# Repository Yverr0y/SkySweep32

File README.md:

# SkySweep32

Open-source passive multi-band RF monitor and logger built around ESP32-S3.

**855–925 MHz · 2.4 GHz · 5.8 GHz · BLE/Wi-Fi · GNSS · microSD · Web UI**

[English](#english) | [Русский](#russian)

---

## English

SkySweep32 Rev C combines three passive RF observation paths with local
logging, positioning, a display, battery operation, and networking in one
open-source device.

> **Rev C is the current hardware revision.** It is ready for its first
> physical prototype. No Rev C board has yet been physically bench-tested.

### Start here

- [Build Rev C](BUILD_THIS.md) — one concise route to the current prototype.
- [Hardware](hardware/rev_c/README.md) — schematic, PCB, BOM, enclosure, and
  source-of-truth hierarchy.
- [Firmware](#firmware-compatibility) — build the canonical ESP32-S3 target.
- [Roadmap](hardware/rev_c/ROADMAP.md) — physical evidence before refinement.
- [Validation](hardware/rev_c/validation/verification_summary.json) — current
  reproducible CAD/build evidence and its limits.
- [Website](https://bobberdolle1.github.io/SkySweep32/) — product overview in
  English and Russian.

### What SkySweep32 does

- **855–925 MHz:** E07-900M10S/CC1101 channelized RSSI and activity
  observation. 433 MHz is outside the Rev C contract.
- **2.4 GHz:** E28-2G4M12SX/SX1281 instantaneous-RSSI sweep with a dedicated
  internal U.FL antenna.
- **5.8 GHz:** RX5808-based eight-channel analog RSSI observation from
  5645–5945 MHz. Every procured lot needs the documented incoming check.
- **Local device functions:** GNSS logging, microSD storage, OLED status,
  buttons/buzzer, protected battery operation, native USB, Wi-Fi dashboard,
  BLE receive functions, and ESP-NOW source support.

These are passive energy/RSSI observation paths. They do not identify a
protocol or transmitter, demodulate video, provide RF direction finding, or
perform active RF interference.

### Rev C hardware

- `ESP32-S3-WROOM-1-N16R8` with native USB-C programming.
- Ebyte `E07-900M10S`, Ebyte `E28-2G4M12SX`/SX1281, and a
  procurement-qualified `RX5808-2012-12P` envelope.
- u-blox `SAM-M10Q-00B`, Molex `104031-0811` microSD socket, and Adafruit
  `PID 326` OLED on a keyed harness.
- Protected USB-C/battery power path using BQ24074, TPS61232, MAX17048, and
  AP63203WU-7 with the specified protected Adafruit `PID 328` battery.
- 150 × 95 mm four-layer PCB with a continuous L2 ground reference.
- 165.4 × 117.4 × 33.5 mm printed indoor enclosure generated around the PCBA,
  battery, display, antennas, harnesses, and M3 hardware. It is not sealed or
  IP rated.

See the [Rev C architecture](hardware/rev_c/ARCHITECTURE.md) and
[exact component manifest](hardware/rev_c/hardware_manifest.json) for the
canonical implementation.

### Capabilities and limits

`Implemented in source` is not physical validation.

| Capability | Rev C implementation | Current limit |
|---|---|---|
| 855–925 MHz observation | E07/CC1101 RSSI/activity | RF response unmeasured; no protocol identity |
| 2.4 GHz observation | E28/SX1281 instantaneous RSSI | Coarse energy/activity only; no demodulation |
| 5.8 GHz observation | RX5808 channel selection + analog RSSI | Supplier/pinout and RF response need physical checks |
| Wi-Fi / BLE | ESP32-S3 dashboard and receive functions | No physical Rev C run; Remote ID has no conformance evidence |
| GNSS / storage / display | Exact fitted modules and source support | No live-fix, endurance, or physical UI test |
| ESP-NOW | Source support | No range, coexistence, or multi-node bench test |
| TinyML | Excluded from Rev C | Legacy source has a dummy model; trained inference is not implemented |
| LoRa / Meshtastic | Excluded from Rev C motherboard | A possible future external expansion, not Rev C hardware |

### Build and validation

[BUILD_THIS.md](BUILD_THIS.md) is the builder entrypoint. It links to the
fitted BOM, fabrication package, enclosure, assembly procedure, canonical
firmware, and prototype checklist without mixing revisions.

The detailed [Rev C build guide](hardware/rev_c/BUILD.md) requires the
complete local gate before purchase:

```bash
python hardware/rev_c/verify_schematic_parity.py
python hardware/verify.py
```

The verification record includes ERC/DRC results, precise exclusion audit,
CAD interference checks, fabrication exports, and the firmware build. These
are design/CAD results only; they do not establish RF performance, reliability,
compliance, manufacturing yield, or field operation.

### Firmware compatibility

Build the current hardware from source only:

```bash
pio run -e esp32s3_rev_c_passive
pio run -e esp32s3_rev_c_passive --target upload
```

> **Do not flash `v0.6.1` binaries onto Rev C.** They target legacy ESP32 DevKit
> wiring. `esp32dev_base`, `esp32dev_standard`, `esp32dev_pro`, and
> `esp32s3_rev_b_pro` remain compile-checked only for historical regression;
> their pin maps, BOMs, enclosures, and release binaries are incompatible with
> Rev C.

### Validation and engineering history

[Validation](hardware/rev_c/validation/verification_summary.json) records the
exact tools, source revision, commands, evidence paths, ERC/DRC results, and
narrow documented exclusions. A skipped gate is recorded as skipped, never as
passed.

Rev C is the only current hardware source. [Rev B](hardware/rev_b/) is a failed
and unverified historical baseline; [Rev A](hardware/LEGACY_REV_A_STATUS.md) is
legacy parser-compatibility history. Neither may be ordered or used to build
Rev C. See the [engineering audit](hardware/ENGINEERING_AUDIT_2026-08-11.md)
for the evidence.

### License and lawful use

GNU GPL v3. Passive reception can still be regulated and can expose private or
protected information. Follow local radio, privacy, aviation, and data laws.
The canonical hardware contains no active interference functions.

---

## Русский

SkySweep32 Rev C объединяет три тракта пассивного RF-наблюдения с локальным
журналированием, позиционированием, дисплеем, питанием от аккумулятора и
сетевыми функциями в одном open-source устройстве.

> **Rev C — текущая аппаратная ревизия.** Она готова к первому физическому
> прототипу. Физическая плата Rev C ещё не прошла стендовые испытания.

### Начните отсюда

- [Собрать Rev C](BUILD_THIS.md) — короткий маршрут к текущему прототипу.
- [Аппаратная часть](hardware/rev_c/README.md) — схема, PCB, BOM, корпус и
  иерархия источников истины.
- [Прошивка](#совместимость-прошивки) — сборка канонической цели ESP32-S3.
- [Дорожная карта](hardware/rev_c/ROADMAP.md) — сначала физические измерения,
  затем изменения.
- [Валидация](hardware/rev_c/validation/verification_summary.json) —
  воспроизводимые CAD/build-проверки и их ограничения.
- [Сайт проекта](https://bobberdolle1.github.io/SkySweep32/).

### Что делает SkySweep32

- **855–925 МГц:** E07-900M10S/CC1101, канальное пассивное наблюдение RSSI и
  активности. 433 МГц не входит в контракт Rev C.
- **2.4 ГГц:** E28-2G4M12SX/SX1281, обзор мгновенного RSSI с отдельной
  внутренней антенной U.FL.
- **5.8 ГГц:** RX5808, восемь каналов и аналоговый RSSI в диапазоне
  5645–5945 МГц. Каждая закупленная партия требует входного контроля.
- **Локальные функции:** GNSS-журналирование, microSD, OLED, кнопки/зуммер,
  защищённое аккумуляторное питание, native USB, Wi-Fi dashboard, приёмные
  BLE-функции и исходная поддержка ESP-NOW.

Это пассивное наблюдение энергии/RSSI. Устройство не определяет протокол или
передатчик, не демодулирует видео, не выполняет радиопеленгацию и не создаёт
активные радиопомехи.

### Аппаратная часть Rev C

- `ESP32-S3-WROOM-1-N16R8` с программированием через native USB-C.
- Ebyte `E07-900M10S`, Ebyte `E28-2G4M12SX`/SX1281 и проверяемый при приёмке
  габарит `RX5808-2012-12P`.
- u-blox `SAM-M10Q-00B`, разъём microSD Molex `104031-0811` и OLED Adafruit
  `PID 326` на ключевом шлейфе.
- Защищённый тракт USB-C/аккумулятора: BQ24074, TPS61232, MAX17048,
  AP63203WU-7 и защищённый аккумулятор Adafruit `PID 328`.
- Четырёхслойная PCB 150 × 95 мм с непрерывной землёй L2.
- Печатный корпус для помещения 165.4 × 117.4 × 33.5 мм, спроектированный
  вокруг PCBA, аккумулятора, дисплея, антенн, шлейфов и крепежа M3. Он не
  герметичен и не имеет IP-рейтинга.

Каноническая реализация описана в [архитектуре Rev C](hardware/rev_c/ARCHITECTURE.md)
и [точном манифесте компонентов](hardware/rev_c/hardware_manifest.json).

### Возможности и ограничения

`Реализовано в исходном коде` не означает физическую проверку.

| Возможность | Реализация Rev C | Текущее ограничение |
|---|---|---|
| Наблюдение 855–925 МГц | E07/CC1101, RSSI/активность | RF-отклик не измерен; протокол не определяется |
| Наблюдение 2.4 ГГц | E28/SX1281, мгновенный RSSI | Только энергия/активность; без демодуляции |
| Наблюдение 5.8 ГГц | RX5808, каналы + аналоговый RSSI | Нужны входной контроль и RF-измерения |
| Wi-Fi / BLE | Dashboard и приёмные функции ESP32-S3 | Нет запуска на физической Rev C; Remote ID без доказательств соответствия |
| GNSS / storage / display | Точные установленные модули и исходный код | Нет live-fix, endurance или физического UI-теста |
| ESP-NOW | Поддержка в исходном коде | Нет стендовых дальностных и multi-node тестов |
| TinyML | Исключён из Rev C | В legacy-коде фиктивная модель; обученной модели нет |
| LoRa / Meshtastic | Исключён из материнской платы Rev C | Возможное внешнее расширение в будущем, не аппаратная часть Rev C |

### Сборка и валидация

[BUILD_THIS.md](BUILD_THIS.md) — входная страница для сборщика. Она связывает
точный BOM, fabrication package, корпус, инструкцию сборки, каноническую
прошивку и чек-лист прототипа без смешения ревизий.

Подробное [руководство Rev C](hardware/rev_c/BUILD.md) требует перед заказом
выполнить:

```bash
python hardware/rev_c/verify_schematic_parity.py
python hardware/verify.py
```

Запись валидации содержит ERC/DRC, точный аудит исключений, CAD-проверки
коллизий, производственные файлы и сборку прошивки. Это результаты CAD/build,
а не доказательство RF-характеристик, надёжности, соответствия нормам,
производственного выхода или полевой работы.

### Совместимость прошивки

Для текущего устройства собирайте прошивку только из исходного кода:

```bash
pio run -e esp32s3_rev_c_passive
pio run -e esp32s3_rev_c_passive --target upload
```

> **Не прошивайте Rev C бинарными файлами `v0.6.1`.** Они относятся к старой
> разводке ESP32 DevKit. `esp32dev_base`, `esp32dev_standard`, `esp32dev_pro` и
> `esp32s3_rev_b_pro` остались только для compile-check исторических регрессий;
> их pin map, BOM, корпуса и release binaries несовместимы с Rev C.

### Валидация и инженерная история

[Валидация](hardware/rev_c/validation/verification_summary.json) фиксирует
точные инструменты, исходную ревизию, команды, пути к evidence, результаты
ERC/DRC и узкие документированные исключения. Пропущенная проверка всегда
записывается как skipped, а не passed.

Rev C — единственный текущий источник аппаратной части. [Rev B](hardware/rev_b/)
— неудачная и непроверенная историческая база, а
[Rev A](hardware/LEGACY_REV_A_STATUS.md) — legacy-история parser compatibility.
Их нельзя заказывать или использовать для сборки Rev C. Доказательства собраны
в [инженерном аудите](hardware/ENGINEERING_AUDIT_2026-08-11.md).

### Лицензия и законное использование

GNU GPL v3. Пассивный приём может регулироваться законом и может раскрывать
частные или защищённые данные. Соблюдайте местные нормы радио-, privacy-,
aviation- и data-law. Каноническая аппаратная часть не содержит активных помех.

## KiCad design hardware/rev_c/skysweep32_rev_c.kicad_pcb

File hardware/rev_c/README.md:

# SkySweep32 Rev C Passive Monitor

## Maturity

**READY FOR FIRST PHYSICAL PROTOTYPE — NOT PRODUCTION VALIDATED**

Rev C is the only canonical current hardware revision. KiCad 10 ERC/DRC,
firmware compilation, fabrication export, full-PCBA STEP generation, and
FreeCAD interference/service-envelope checks are reproducible from this
directory. No Rev C board has been assembled or powered. The package supports
one engineering prototype spin whose bring-up may require changes; it is not a
mass-production release.

Rev A and Rev B are historical, incompatible, and non-orderable. The revision
decision is in [`ADR_001_NEW_REVISION.md`](ADR_001_NEW_REVISION.md).

## Product boundary

Rev C is a passive receive/energy-observation instrument. It has no RF jamming,
protocol-injection, GPS-denial, LoRa, trained TinyML inference, or RF
direction-finding hardware.

| Function | Rev C implementation | Evidence boundary |
|---|---|---|
| 855–925 MHz | Ebyte `E07-900M10S` / CC1101 RSSI and activity | Schematic/layout checked; RF response unmeasured; no 433 MHz operation |
| 2.4 GHz | Ebyte `E28-2G4M12SX` / SX1281 RSSI sweep | Firmware contract and CAD checked; no RF calibration or protocol identity |
| 5.8 GHz | Qualified-envelope `RX5808-2012-12P`, eight selected channels and analog RSSI | Source/pinout/calibration must pass incoming inspection and bench test |
| Wi-Fi/BLE | ESP32-S3 receive functions, web UI, ESP-NOW, experimental Remote ID | Firmware compiles; no physical or standards-conformance test |
| Position/time | u-blox `SAM-M10Q-00B` | UART/TIMEPULSE contract checked; no live-fix test |
| Storage | Molex `104031-0811` microSD | SPI/card-detect contract checked; no card test |
| Display/controls | Adafruit PID 326 OLED on PID 4210 keyed cable, LED, buzzer, three buttons | CAD fit/actuation checked; no physical operation test |
| Portable power | Adafruit PID 328 protected 1S LiPo through BQ24074 power path | Electrical/CAD design checked; charge, runtime, thermal, and safety behavior unmeasured |

The exact parts, GPIO allocation, exclusions, power contract, assembly items,
and mechanical datums are in
[`hardware_manifest.json`](hardware_manifest.json). Manufacturer documentation
defines physical reality; the KiCad schematic and PCB define the manufactured
circuit and geometry.

## Electrical design

- MCU: Espressif `ESP32-S3-WROOM-1-N16R8`, 16 MB flash and 8 MB octal PSRAM.
- USB: GCT `USB4105-GF-A`; 5 V source rated at least 2 A; 5.1 kΩ CC pull-downs;
  no USB-PD voltage negotiation.
- Protection: Bourns `MF-MSMF200-2`, Littelfuse `SMAJ5.0A`, and ST
  `USBLC6-2SC6`.
- Battery/power path: Adafruit `PID 328 / LP785060` protected 1S pack,
  `BQ24074RGTR` at 800 mA charge and 1.3 A input limit.
- Rails: `TPS61232DRCR` fixed 5 V boost with `SRN6028C-1R0Y`, then
  `AP63203WU-7` 3.3 V / 2 A buck with `SRN6028-3R9M`.
- Encoded peak estimate: 1.35 A. This is a design input, not a measured current
  or thermal result.
- Programming: native ESP32-S3 USB, manual BOOT/RESET, and labelled UART0 and
  power test pads.
- Optional vibration output parts are DNP and excluded from fitted BOM and
  placement exports.

## Build this revision

Use [BUILD.md](BUILD.md) as the single first-prototype procurement, assembly,
and source-build path. It links the exact fabrication package, fitted BOM,
non-PCB accessories, first-power limits, and canonical PlatformIO environment.
Do not use any Rev A/Rev B document or `v0.6.1` binary for Rev C.

The hierarchy starts at
[`skysweep32_rev_c.kicad_sch`](skysweep32_rev_c.kicad_sch): overview plus five
functional sheets for power, control/alerts, 2.4 GHz/sub-GHz, 5.8 GHz, and
GNSS/storage/display. `verify_schematic_parity.py` proves its named
reference/pin/net contract against the pre-hierarchy review baseline.

The native KiCad schematic is
[`skysweep32_rev_c.kicad_sch`](skysweep32_rev_c.kicad_sch). Fresh unexcluded
ERC evidence is [`validation/erc.rpt`](validation/erc.rpt); the eight narrowly
documented stock-symbol footprint-filter exceptions are machine-audited in
[`validation/erc_exclusions.json`](validation/erc_exclusions.json).

## PCB construction and routing

Board: 150.0 × 95.0 mm, 1.6 mm nominal, four layers, 3.0 mm corner radius, and
four Ø3.2 mm mounting holes on a 140 × 85 mm pattern.

| Layer | Function | Nominal construction |
|---|---|---|
| L1 / F.Cu | components, USB/RF/power signals, local ground pour | 35 µm copper |
| L2 / GND_PLANE | continuous signal reference plane | 0.18 mm L1–L2 dielectric, 35 µm copper |
| L3 / POWER_PLANE | 3V3 distribution and secondary routing | 1.10 mm core, 35 µm copper |
| L4 / B.Cu | secondary signals and ground pour | 0.18 mm L3–L4 dielectric, 35 µm copper |

Fabricator requirements: FR-4, ENIG, minimum 0.20 mm copper spacing, minimum
0.20 mm finished drill, 0.25 mm default signals, 0.8 mm nominal power traces,
and 0.6/0.3 mm nominal via diameter/drill. USB D+/D− use a 0.25/0.25 mm nominal
geometry and must be field-solver adjusted for 90 Ω differential using the
fabricator's actual stackup. J5 and J7 use short 0.30 mm nominal RF launches and
likewise require 50 Ω confirmation.

L2 remains continuous under signal routes. Antenna keepouts for the
ESP32-S3, GNSS, E28, and E07 paths are free of unrelated copper and parts. The
layout's DRC result proves only the encoded KiCad rules; RF response, USB signal
integrity, power integrity, and manufacturing yield remain unmeasured.

Fresh unexcluded DRC evidence is [`validation/drc.rpt`](validation/drc.rpt).
[`validation/drc_exclusions.json`](validation/drc_exclusions.json) records the
single audited `TPS61232` mixed SMD/thermal-via footprint-type exception.
TP1–TP5 expose protected VBUS, 3V3, GND, UART0 TX, and UART0 RX with the lid
removed.

## Mechanical system

The enclosure generator consumes the complete KiCad PCBA STEP. It includes:

- a protected PID 328 battery bay below the PCBA;
- four DIN 912 M3 × 30 screws, DIN 934 M3 nut traps, PCB supports, and lid
  compression posts at the actual mounting holes;
- USB-C insertion, microSD removal, J5/J7 SMA plug, and external antenna service
  envelopes;
- Adafruit PID 2308 internal 2.4 GHz antenna and its 100 mm U.FL cable envelope;
- lid-mounted Adafruit PID 326 OLED and PID 4210 100 mm cable envelope;
- checked closed and 30 mm-open cable routes;
- independent RESET, BOOT, and USER plungers plus status-LED aperture;
- base, lid, button, service-envelope, open/closed/exploded/cutaway STEP files
  and printable STL parts.

The checked closed outer envelope is 165.4 × 117.4 × 33.5 mm. The case is an
indoor printed enclosure, not sealed and not IP rated. Start the first-fit PETG
print at 0.20 mm layers, four perimeters, and 30% infill. Measure one complete
print and the first PCBA before any batch.

- Generator: [`generate_enclosure.py`](generate_enclosure.py)
- Interface drawing:
  [`enclosure/rev_c_mechanical_drawing.svg`](enclosure/rev_c_mechanical_drawing.svg)
- Machine report:
  [`enclosure/mechanical_validation.json`](enclosure/mechanical_validation.json)
- Assembly/bring-up: [`ASSEMBLY_AND_BRINGUP.md`](ASSEMBLY_AND_BRINGUP.md)
- Physical checks:
  [`PROTOTYPE_VALIDATION_CHECKLIST.md`](PROTOTYPE_VALIDATION_CHECKLIST.md)

Custom RF/GNSS/OLED/battery STEP bodies are explicitly conservative mechanical
envelopes built from referenced drawings. They are not manufacturer precision
CAD. Standard KiCad models are used only where package geometry was checked.
CAD collision checks do not replace sample measurement.

## Evidence roadmap

[ROADMAP.md](ROADMAP.md) defines the mandatory first-board measurements and
the evidence that could justify a later revision. It is deliberately separate
from the current fabrication package: no future feature is part of Rev C until
the required evidence exists.

## Reproducible verification

Requirements are pinned in [`../toolchain.json`](../toolchain.json). From the
repository root:

```bash
python hardware/verify.py
```

The command checks the generated firmware contract, runs ERC/DRC, rebuilds
mechanical envelopes and the PCBA STEP, regenerates case/assembly/drawing files,
runs collision, cable-length, and service-volume checks, regenerates fabrication
files, builds `esp32s3_rev_c_passive`, and refreshes renders. A deliberately
skipped gate is recorded as `SKIPPED`, never `PASS`.

Primary outputs:

- [`validation/verification_summary.json`](validation/verification_summary.json)
- [`manufacturing/fabrication_manifest.json`](manufacturing/fabrication_manifest.json)
- [`manufacturing/bom_fitted.csv`](manufacturing/bom_fitted.csv)
- [`manufacturing/assembly_items.csv`](manufacturing/assembly_items.csv)
- [`manufacturing/positions.csv`](manufacturing/positions.csv)
- [`manufacturing/assembly_top.svg`](manufacturing/assembly_top.svg) and
  [`manufacturing/assembly_bottom.svg`](manufacturing/assembly_bottom.svg):
  primary zoomable fitted-placement/orientation drawings; use
  `positions.csv` for machine assembly and
  [`ASSEMBLY_AND_BRINGUP.md`](ASSEMBLY_AND_BRINGUP.md) for the sequence.
- [`manufacturing/skysweep32_rev_c_gerbers.zip`](manufacturing/skysweep32_rev_c_gerbers.zip)

Do not infer `PROTOTYPE_ASSEMBLED`, `BENCH_TESTED`, `FIELD_TESTED`, or
`PRODUCTION_VALIDATED` from any generated file.

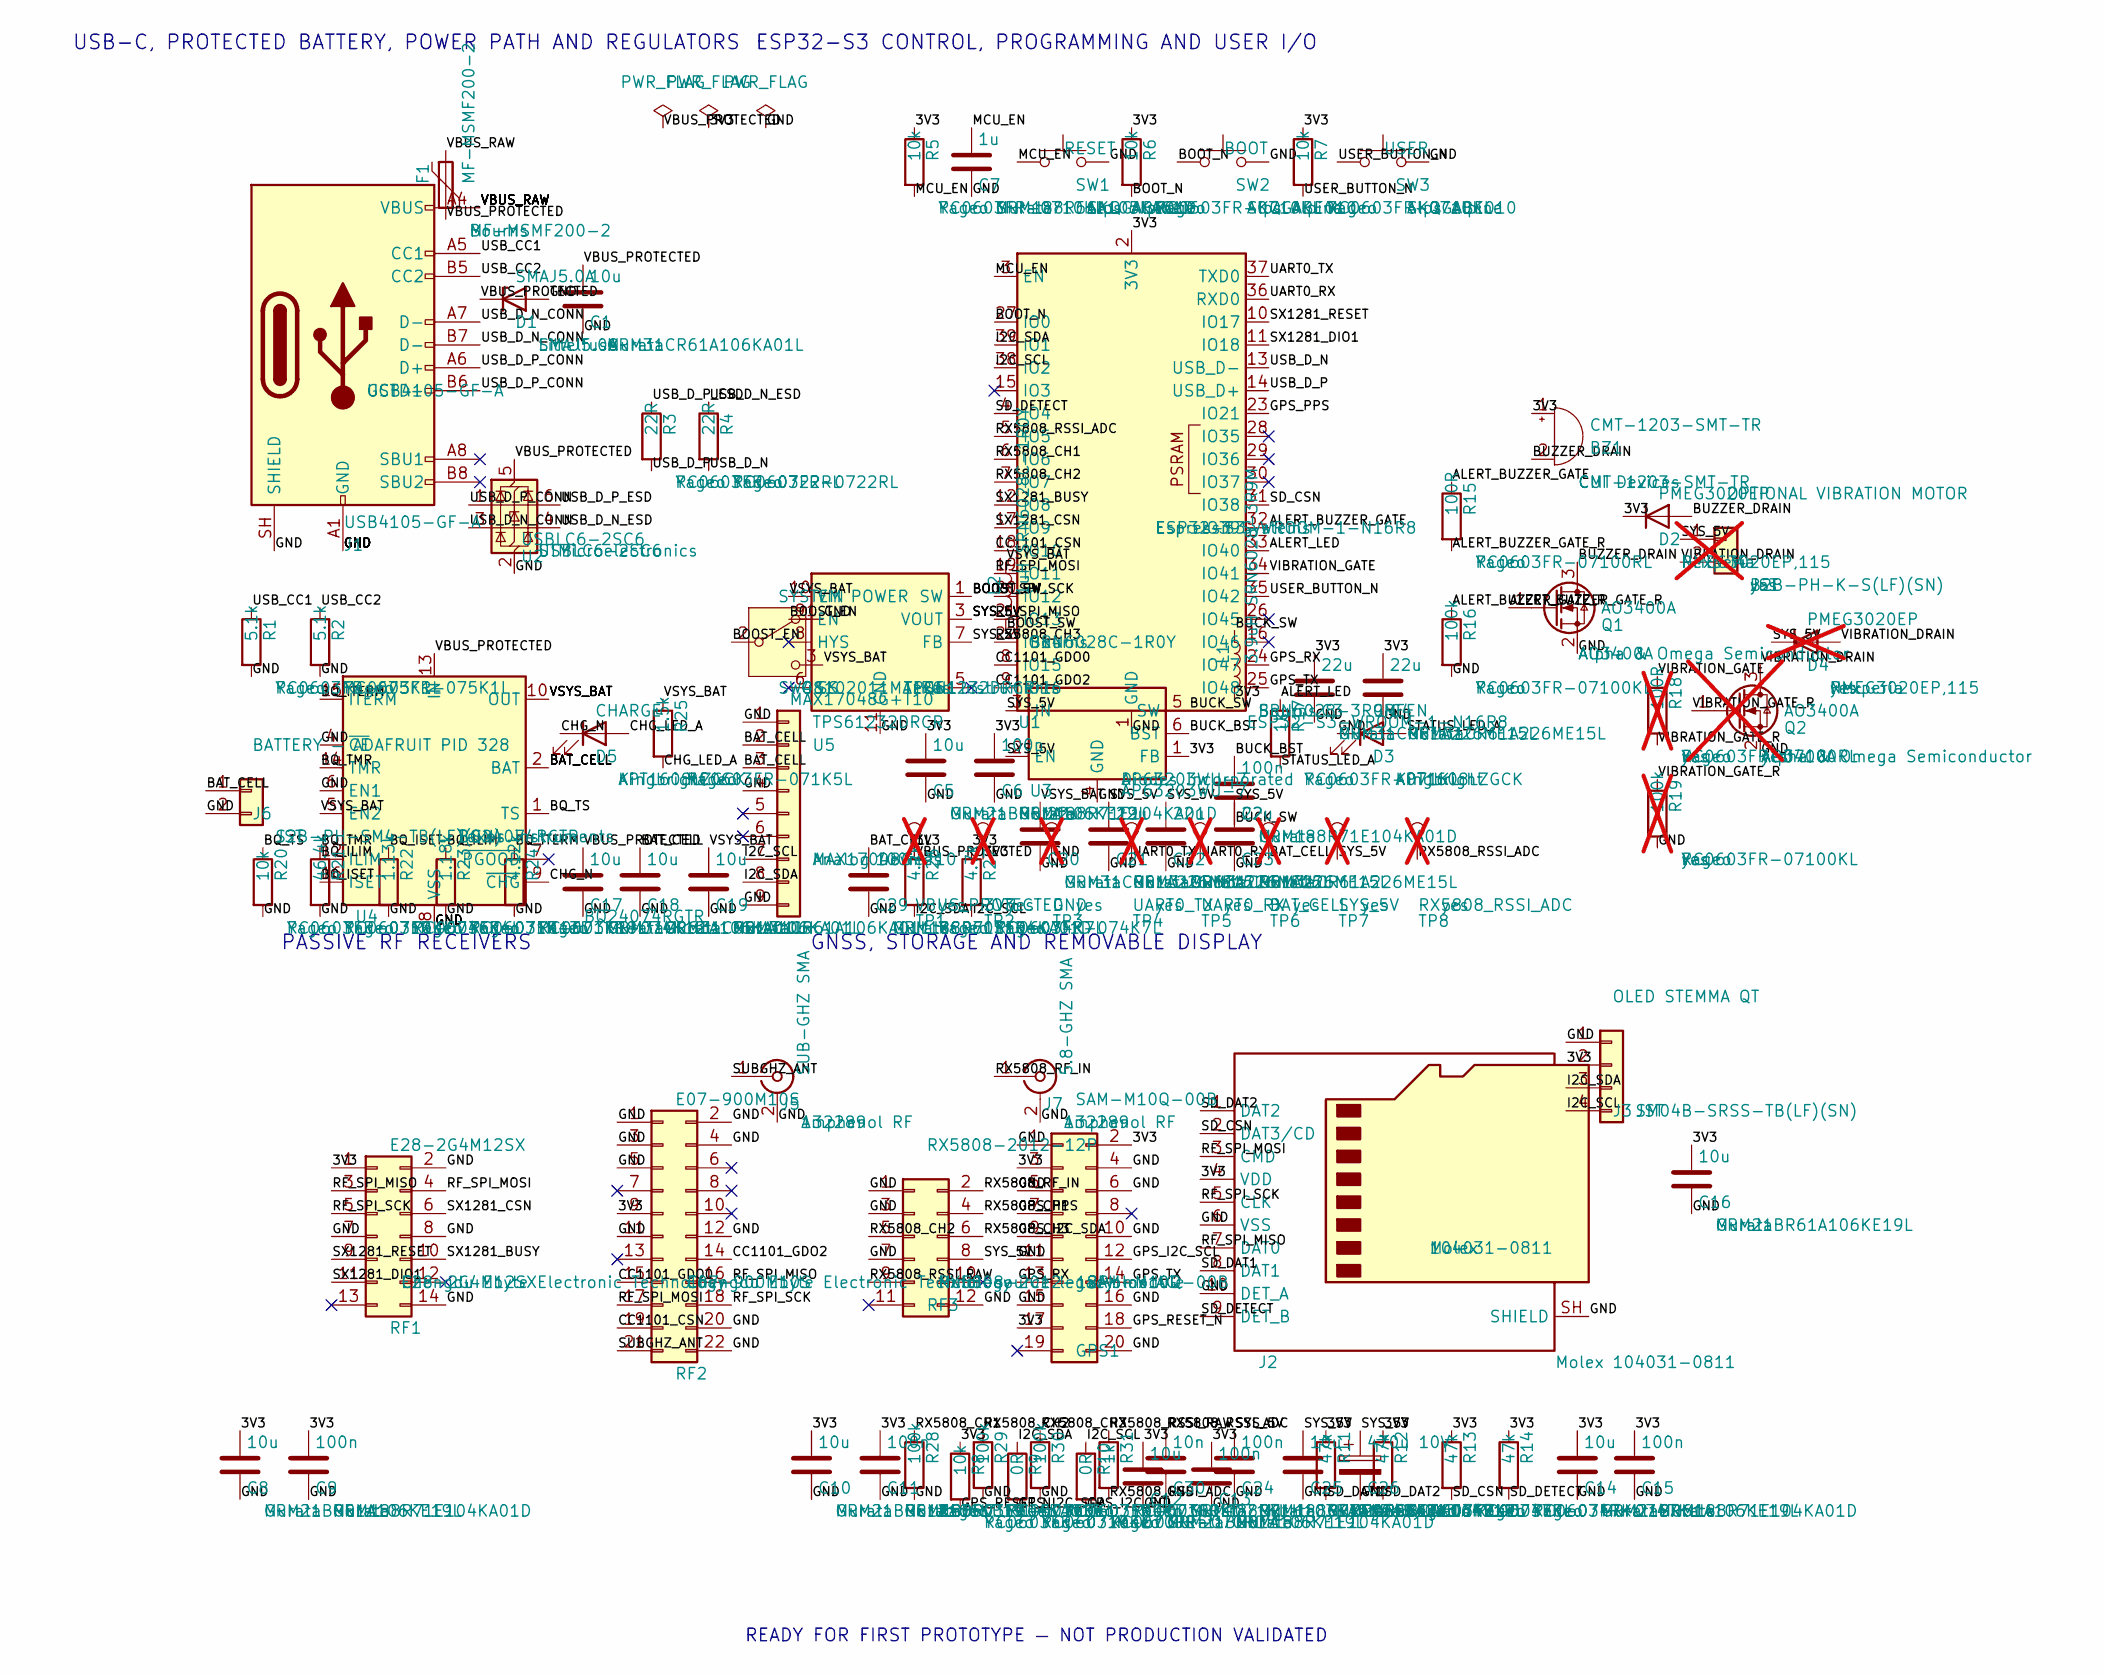
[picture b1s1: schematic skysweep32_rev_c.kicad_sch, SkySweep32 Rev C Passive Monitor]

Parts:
BZ1: CMT-1203-SMT-TR; Buzzer_CUI_CMT_1203_SMT_TR; MPN CMT-1203-SMT-TR
C1, C17, C18, C19: 10u; C_1206_3216Metric; MPN GRM31CR61A106KA01L
C2, C6, C9, C11, C13, C15, C24, C29: 100n; C_0603_1608Metric; MPN GRM188R71E104KA01D
C3, C4, C20, C21, C22, C23: 22u; C_1206_3216Metric; MPN GRM31CR61A226ME15L
C5, C8, C10, C12, C14, C16, C25: 10u; C_0805_2012Metric; MPN GRM21BR61A106KE19L
C7: 1u; C_0603_1608Metric; MPN GRM188R61A105KA61D
C26: 470u 10V; CP_Elec_10x10; MPN EEE-FK1A471P
C30: 10n; C_0603_1608Metric; MPN GRM188R71H103KA01D
D1: SMAJ5.0A; D_SMA; MPN SMAJ5.0A
D2: PMEG3020EP; D_SOD-128; MPN PMEG3020EP,115
D3: GREEN; LED_0603_1608Metric; MPN APT1608LZGCK
D4: PMEG3020EP; D_SOD-128; MPN PMEG3020EP,115; not fitted
D5: CHARGE; LED_0603_1608Metric; MPN APT1608LZGCK
F1: MF-MSMF200-2; Fuse_1812_4532Metric; MPN MF-MSMF200-2
GPS1: SAM-M10Q-00B; Module_UBlox_SAM_M10Q; MPN SAM-M10Q-00B
J1: USB4105-GF-A; USB_C_Receptacle_GCT_USB4105-xx-A_16P_TopMnt_Horizontal; MPN USB4105-GF-A
J2: Molex 104031-0811; microSD_HC_Molex_104031-0811; MPN 104031-0811
J3: OLED STEMMA QT; JST_SH_SM04B-SRSS-TB_1x04-1MP_P1.00mm_Horizontal; MPN SM04B-SRSS-TB(LF)(SN)
J4: OPTIONAL VIBRATION MOTOR; JST_PH_B2B-PH-K_1x02_P2.00mm_Vertical; MPN B2B-PH-K-S(LF)(SN); not fitted
J5: SUB-GHZ SMA; SMA_Amphenol_132289_EdgeMount; MPN 132289
J6: BATTERY — ADAFRUIT PID 328; JST_PH_S2B-PH-SM4-TB_1x02-1MP_P2.00mm_Horizontal; MPN S2B-PH-SM4-TB(LF)(SN)
J7: 5.8-GHZ SMA; SMA_Amphenol_132289_EdgeMount; MPN 132289
L1: 3.9uH SRN6028-3R9M; L_Bourns-SRN6028; MPN SRN6028-3R9M
L2: 1uH SRN6028C-1R0Y; L_Bourns-SRN6028; MPN SRN6028C-1R0Y
Q1: AO3400A; SOT-23; MPN AO3400A
Q2: AO3400A; SOT-23; MPN AO3400A; not fitted
R1, R2: 5.1k; R_0603_1608Metric; MPN RC0603FR-075K1L
R3, R4: 22R; R_0603_1608Metric; MPN RC0603FR-0722RL
R5, R6, R7, R8, R20: 10k; R_0603_1608Metric; MPN RC0603FR-0710KL
R9, R10: 0R; R_0603_1608Metric; MPN RC0603JR-070RL
R11, R12, R13, R14: 47k; R_0603_1608Metric; MPN RC0603FR-0747KL
R15: 100R; R_0603_1608Metric; MPN RC0603FR-07100RL
R16, R28, R29, R30: 100k; R_0603_1608Metric; MPN RC0603FR-07100KL
R17, R31: 1k; R_0603_1608Metric; MPN RC0603FR-071KL
R18: 100R; R_0603_1608Metric; MPN RC0603FR-07100RL; not fitted
R19: 100k; R_0603_1608Metric; MPN RC0603FR-07100KL; not fitted
R21: 46.4k; R_0603_1608Metric; MPN RC0603FR-0746K4L
R22: 1.13k; R_0603_1608Metric; MPN RC0603FR-071K13L
R23: 1.18k; R_0603_1608Metric; MPN RC0603FR-071K18L
R24: 4.12k; R_0603_1608Metric; MPN RC0603FR-074K12L
R25: 1.5k; R_0603_1608Metric; MPN RC0603FR-071K5L
R26, R27: 4.7k; R_0603_1608Metric; MPN RC0603FR-074K7L
RF1: E28-2G4M12SX; Module_Ebyte_E28_2G4M12SX; MPN E28-2G4M12SX
RF2: E07-900M10S; Module_Ebyte_E07_900M10S; MPN E07-900M10S
RF3: RX5808-2012-12P; Module_RX5808_2012_12P; MPN RX5808-2012-12P
SW1: RESET; SW_SPST_SKQG_WithoutStem; MPN SKQGABE010
SW2: BOOT; SW_SPST_SKQG_WithoutStem; MPN SKQGABE010
SW3: USER; SW_SPST_SKQG_WithoutStem; MPN SKQGABE010
SW4: SYSTEM POWER; SW_Slide_SPDT_Angled_CK_OS102011MA1Q; MPN OS102011MA1QN1
TP1: VBUS_PROTECTED; TestPoint_Pad_D1.0mm; not fitted
TP2: 3V3; TestPoint_Pad_D1.0mm; not fitted
TP3: GND; TestPoint_Pad_D1.0mm; not fitted
TP4: UART0_TX; TestPoint_Pad_D1.0mm; not fitted
TP5: UART0_RX; TestPoint_Pad_D1.0mm; not fitted
TP6: BAT_CELL; TestPoint_Pad_D1.0mm; not fitted
TP7: SYS_5V; TestPoint_Pad_D1.0mm; not fitted
TP8: RX5808_RSSI_ADC; TestPoint_Pad_D1.0mm; not fitted
U1: ESP32-S3-WROOM-1-N16R8; ESP32-S3-WROOM-1; MPN ESP32-S3-WROOM-1-N16R8
U2: USBLC6-2SC6; SOT-23-6; MPN USBLC6-2SC6
U3: AP63203WU-7; TSOT-23-6; MPN AP63203WU-7
U4: BQ24074RGTR; VQFN-16-1EP_3x3mm_P0.5mm_EP1.6x1.6mm; MPN BQ24074RGTR
U5: TPS61232DRCR; Texas_S-PVSON-N10_ThermalVias; MPN TPS61232DRCR
U6: MAX17048G+T10; DFN-8-1EP_2x2mm_P0.5mm_EP0.9x1.3mm; MPN MAX17048G+T10

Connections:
3V3: BZ1.1 (+), C3.1, C4.1, C5.1, C6.1, C8.1, C9.1, C10.1, C11.1, C12.1, C13.1, C14.1, C15.1, C16.1, D2.1 (K), GPS1.2, GPS1.3, GPS1.17, J2.4 (VDD), J3.2, L1.2, R5.1, R6.1, R7.1, R8.1, R11.1, R12.1, R13.1, R14.1, R26.1, R27.1, RF1.1, RF2.9, TP2.1, U1.2 (3V3), U3.1 (FB)
ALERT_BUZZER_GATE: R15.1, U1.32 (IO39)
ALERT_BUZZER_GATE_R: Q1.1 (G), R15.2, R16.1
ALERT_LED: R17.1, U1.33 (IO40)
BAT_CELL: C18.1, C29.1, J6.1, TP6.1, U4.2 (BAT), U4.3 (BAT), U6.2, U6.3
BOOST_EN: SW4.2 (B), U5.9 (EN)
BOOST_SW: L2.2, U5.1 (SW), U5.2 (SW)
BOOT_N: R6.2, SW2.1, U1.27 (IO0)
BQ_ILIM: R23.1, U4.12 (ILIM)
BQ_ISET: R22.1, U4.16 (ISET)
BQ_ITERM: R24.1, U4.15 (ITERM)
BQ_TMR: R21.1, U4.14 (TMR)
BQ_TS: R20.1, U4.1 (TS)
BUCK_BST: C2.1, U3.6 (BST)
BUCK_SW: C2.2, L1.1, U3.5 (SW)
BUZZER_DRAIN: BZ1.2 (-), D2.2 (A), Q1.3 (D)
CC1101_CSN: RF2.19, U1.18 (IO10)
CC1101_GDO0: RF2.15, U1.8 (IO15)
CC1101_GDO2: RF2.14, U1.9 (IO16)
CHG_LED_A: D5.2 (A), R25.2
CHG_N: D5.1 (K), U4.9 (~CHG)
GND: C1.2, C3.2, C4.2, C5.2, C6.2, C7.2, C8.2, C9.2, C10.2, C11.2, C12.2, C13.2, C14.2, C15.2, C16.2, C17.2, C18.2, C19.2, C20.2, C21.2, C22.2, C23.2, C24.2, C25.2, C26.2, C29.2, C30.2, D1.2 (A), D3.1 (K), GPS1.1, GPS1.4, GPS1.5, GPS1.6, GPS1.10, GPS1.11, GPS1.15, GPS1.16, GPS1.20, J1.A1 (GND), J1.A12 (GND), J1.B1 (GND), J1.B12 (GND), J1.SH (SHIELD), J2.6 (VSS), J2.10 (DET_A), J2.SH (SHIELD), J3.1, J5.2 (Ext), J6.2, J7.2 (Ext), Q1.2 (S), Q2.2 (S), R1.2, R2.2, R16.2, R19.2, R20.2, R21.2, R22.2, R23.2, R24.2, R28.2, R29.2, R30.2, RF1.2, RF1.7, RF1.8, RF1.14, RF2.1, RF2.2, RF2.3, RF2.4, RF2.5, RF2.11, RF2.12, RF2.20, RF2.22, RF3.1, RF3.3, RF3.7, RF3.12, SW1.2, SW2.2, SW3.2, SW4.1 (A), TP3.1, U1.1 (GND), U1.40 (GND), U1.41 (GND), U2.2 (GND), U3.4 (GND), U4.4 (~CE), U4.6 (EN1), U4.8 (VSS), U4.17 (VSS), U5.11 (GND), U6.1, U6.4, U6.9
GPS_I2C_SCL: GPS1.12, R10.2
GPS_I2C_SDA: GPS1.9, R9.2
GPS_PPS: GPS1.7, U1.23 (IO21)
GPS_RESET_N: GPS1.18, R8.2
GPS_RX: GPS1.13, U1.24 (IO47)
GPS_TX: GPS1.14, U1.25 (IO48)
I2C_SCL: J3.4, R10.1, R27.2, U1.38 (IO2), U6.7
I2C_SDA: J3.3, R9.1, R26.2, U1.39 (IO1), U6.8
MCU_EN: C7.1, R5.2, SW1.1, U1.3 (EN)
RF_SPI_MISO: J2.7 (DAT0), RF1.3, RF2.16, U1.21 (IO13)
RF_SPI_MOSI: J2.3 (CMD), RF1.4, RF2.17, U1.19 (IO11)
RF_SPI_SCK: J2.5 (CLK), RF1.5, RF2.18, U1.20 (IO12)
RX5808_CH1: R28.1, RF3.4, U1.6 (IO6)
RX5808_CH2: R29.1, RF3.5, U1.7 (IO7)
RX5808_CH3: R30.1, RF3.6, U1.22 (IO14)
RX5808_RF_IN: J7.1 (In), RF3.2
RX5808_RSSI_ADC: C30.1, R31.2, TP8.1, U1.5 (IO5)
RX5808_RSSI_RAW: R31.1, RF3.9
SD_CSN: J2.2 (DAT3/CD), R13.2, U1.31 (IO38)
SD_DAT1: J2.8 (DAT1), R11.2
SD_DAT2: J2.1 (DAT2), R12.2
SD_DETECT: J2.9 (DET_B), R14.2, U1.4 (IO4)
STATUS_LED_A: D3.2 (A), R17.2
SUBGHZ_ANT: J5.1 (In), RF2.21
SX1281_BUSY: RF1.10, U1.12 (IO8)
SX1281_CSN: RF1.6, U1.17 (IO9)
SX1281_DIO1: RF1.11, U1.11 (IO18)
SX1281_RESET: RF1.9, U1.10 (IO17)
SYS_5V: C21.1, C22.1, C23.1, C24.1, C25.1, C26.1, D4.1 (K), J4.1, RF3.8, TP7.1, U3.2 (EN), U3.3 (IN), U5.3 (VOUT), U5.4 (VOUT), U5.7 (FB)
UART0_RX: TP5.1, U1.36 (RXD0)
UART0_TX: TP4.1, U1.37 (TXD0)
USB_CC1: J1.A5 (CC1), R1.1
USB_CC2: J1.B5 (CC2), R2.1
USB_D_N: R4.2, U1.13 (USB_D-)
USB_D_N_CONN: J1.A7 (D-), J1.B7 (D-), U2.3 (I/O2)
USB_D_N_ESD: R4.1, U2.4 (I/O2)
USB_D_P: R3.2, U1.14 (USB_D+)
USB_D_P_CONN: J1.A6 (D+), J1.B6 (D+), U2.1 (I/O1)
USB_D_P_ESD: R3.1, U2.6 (I/O1)
USER_BUTTON_N: R7.2, SW3.1, U1.35 (IO42)
VBUS_PROTECTED: C1.1, C17.1, D1.1 (K), F1.2, TP1.1, U2.5 (VBUS), U4.13 (IN)
VBUS_RAW: F1.1, J1.A4 (VBUS), J1.A9 (VBUS), J1.B4 (VBUS), J1.B9 (VBUS)
VIBRATION_DRAIN: D4.2 (A), J4.2, Q2.3 (D)
VIBRATION_GATE: R18.1, U1.34 (IO41)
VIBRATION_GATE_R: Q2.1 (G), R18.2, R19.1
VSYS_BAT: C19.1, C20.1, L2.1, R25.1, SW4.3 (C), U4.5 (EN2), U4.10 (OUT), U4.11 (OUT), U5.10 (VIN)

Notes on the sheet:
USB-C, PROTECTED BATTERY, POWER PATH AND REGULATORS
ESP32-S3 CONTROL, PROGRAMMING AND USER I/O
PASSIVE RF RECEIVERS
GNSS, STORAGE AND REMOVABLE DISPLAY
READY FOR FIRST PROTOTYPE — NOT PRODUCTION VALIDATED

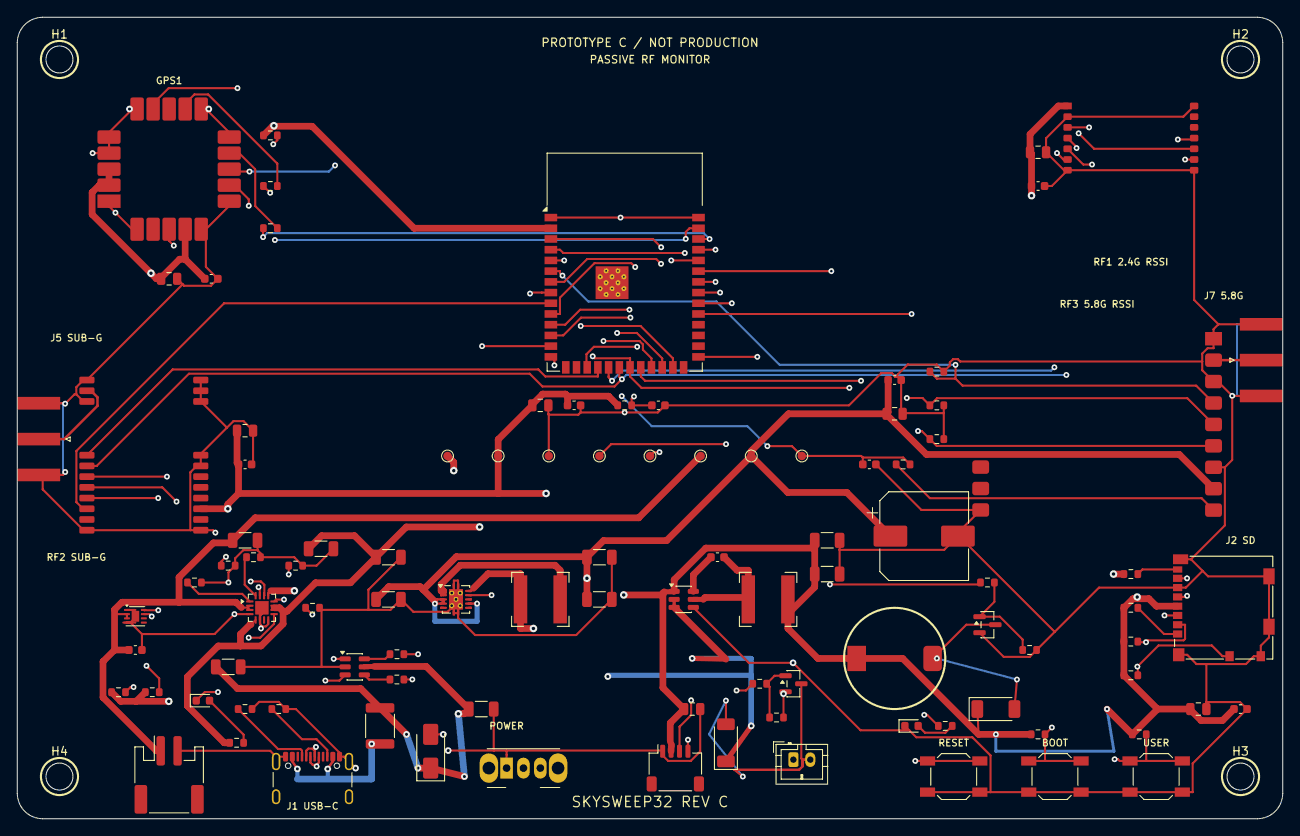
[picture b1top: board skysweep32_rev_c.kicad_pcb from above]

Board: 4 copper layers, 150.0 x 95.0 mm, 103 parts (0 on the bottom side), 68 nets.

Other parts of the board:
H1, H2, H3, H4: M3 NPTH / 10mm FASTENER KEEPOUT; MountingHole_M3_5mm_Keepout

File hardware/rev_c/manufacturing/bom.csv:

"Refs","Value","Footprint","Manufacturer","MPN","Qty","DNP"
"BZ1","CMT-1203-SMT-TR","SkySweep32RevC:Buzzer_CUI_CMT_1203_SMT_TR","CUI Devices","CMT-1203-SMT-TR","1",""
"C1,C17-C19","10u","Capacitor_SMD:C_1206_3216Metric","Murata","GRM31CR61A106KA01L","4",""
"C2,C6,C9,C11,C13,C15,C24,C29","100n","Capacitor_SMD:C_0603_1608Metric","Murata","GRM188R71E104KA01D","8",""
"C3,C4,C20-C23","22u","Capacitor_SMD:C_1206_3216Metric","Murata","GRM31CR61A226ME15L","6",""
"C5,C8,C10,C12,C14,C16,C25","10u","Capacitor_SMD:C_0805_2012Metric","Murata","GRM21BR61A106KE19L","7",""
"C7","1u","Capacitor_SMD:C_0603_1608Metric","Murata","GRM188R61A105KA61D","1",""
"C26","470u 10V","Capacitor_SMD:CP_Elec_10x10","Panasonic","EEE-FK1A471P","1",""
"C30","10n","Capacitor_SMD:C_0603_1608Metric","Murata","GRM188R71H103KA01D","1",""
"D1","SMAJ5.0A","Diode_SMD:D_SMA","Littelfuse","SMAJ5.0A","1",""
"D2","PMEG3020EP","Diode_SMD:D_SOD-128","Nexperia","PMEG3020EP,115","1",""
"D3","GREEN","LED_SMD:LED_0603_1608Metric","Kingbright","APT1608LZGCK","1",""
"D4","PMEG3020EP","Diode_SMD:D_SOD-128","Nexperia","PMEG3020EP,115","1","yes"
"D5","CHARGE","LED_SMD:LED_0603_1608Metric","Kingbright","APT1608LZGCK","1",""
"F1","MF-MSMF200-2","Fuse:Fuse_1812_4532Metric","Bourns","MF-MSMF200-2","1",""
"GPS1","SAM-M10Q-00B","SkySweep32RevC:Module_UBlox_SAM_M10Q","u-blox AG","SAM-M10Q-00B","1",""
"J1","USB4105-GF-A","Connector_USB:USB_C_Receptacle_GCT_USB4105-xx-A_16P_TopMnt_Horizontal","GCT","USB4105-GF-A","1",""
"J2","Molex 104031-0811","Connector_Card:microSD_HC_Molex_104031-0811","Molex","104031-0811","1",""
"J3","OLED STEMMA QT","Connector_JST:JST_SH_SM04B-SRSS-TB_1x04-1MP_P1.00mm_Horizontal","JST","SM04B-SRSS-TB(LF)(SN)","1",""
"J4","OPTIONAL VIBRATION MOTOR","Connector_JST:JST_PH_B2B-PH-K_1x02_P2.00mm_Vertical","JST","B2B-PH-K-S(LF)(SN)","1","yes"
"J5","SUB-GHZ SMA","Connector_Coaxial:SMA_Amphenol_132289_EdgeMount","Amphenol RF","132289","1",""
"J6","BATTERY — ADAFRUIT PID 328","Connector_JST:JST_PH_S2B-PH-SM4-TB_1x02-1MP_P2.00mm_Horizontal","JST","S2B-PH-SM4-TB(LF)(SN)","1",""
"J7","5.8-GHZ SMA","Connector_Coaxial:SMA_Amphenol_132289_EdgeMount","Amphenol RF","132289","1",""
"L1","3.9uH SRN6028-3R9M","Inductor_SMD:L_Bourns-SRN6028","Bourns","SRN6028-3R9M","1",""
"L2","1uH SRN6028C-1R0Y","Inductor_SMD:L_Bourns-SRN6028","Bourns","SRN6028C-1R0Y","1",""
"Q1","AO3400A","Package_TO_SOT_SMD:SOT-23","Alpha & Omega Semiconductor","AO3400A","1",""
"Q2","AO3400A","Package_TO_SOT_SMD:SOT-23","Alpha & Omega Semiconductor","AO3400A","1","yes"
"R1,R2","5.1k","Resistor_SMD:R_0603_1608Metric","Yageo","RC0603FR-075K1L","2",""
"R3,R4","22R","Resistor_SMD:R_0603_1608Metric","Yageo","RC0603FR-0722RL","2",""
"R5-R8,R20","10k","Resistor_SMD:R_0603_1608Metric","Yageo","RC0603FR-0710KL","5",""
"R9,R10","0R","Resistor_SMD:R_0603_1608Metric","Yageo","RC0603JR-070RL","2",""
"R11-R14","47k","Resistor_SMD:R_0603_1608Metric","Yageo","RC0603FR-0747KL","4",""
"R15","100R","Resistor_SMD:R_0603_1608Metric","Yageo","RC0603FR-07100RL","1",""
"R16,R28-R30","100k","Resistor_SMD:R_0603_1608Metric","Yageo","RC0603FR-07100KL","4",""
"R17,R31","1k","Resistor_SMD:R_0603_1608Metric","Yageo","RC0603FR-071KL","2",""
"R18","100R","Resistor_SMD:R_0603_1608Metric","Yageo","RC0603FR-07100RL","1","yes"
"R19","100k","Resistor_SMD:R_0603_1608Metric","Yageo","RC0603FR-07100KL","1","yes"
"R21","46.4k","Resistor_SMD:R_0603_1608Metric","Yageo","RC0603FR-0746K4L","1",""
"R22","1.13k","Resistor_SMD:R_0603_1608Metric","Yageo","RC0603FR-071K13L","1",""
"R23","1.18k","Resistor_SMD:R_0603_1608Metric","Yageo","RC0603FR-071K18L","1",""
"R24","4.12k","Resistor_SMD:R_0603_1608Metric","Yageo","RC0603FR-074K12L","1",""
"R25","1.5k","Resistor_SMD:R_0603_1608Metric","Yageo","RC0603FR-071K5L","1",""
"R26,R27","4.7k","Resistor_SMD:R_0603_1608Metric","Yageo","RC0603FR-074K7L","2",""
"RF1","E28-2G4M12SX","SkySweep32RevC:Module_Ebyte_E28_2G4M12SX","Chengdu Ebyte Electronic Technology","E28-2G4M12SX","1",""
"RF2","E07-900M10S","SkySweep32RevC:Module_Ebyte_E07_900M10S","Chengdu Ebyte Electronic Technology","E07-900M10S","1",""
"RF3","RX5808-2012-12P","SkySweep32RevC:Module_RX5808_2012_12P","Multi-source legacy module","RX5808-2012-12P","1",""
"SW1","RESET","Button_Switch_SMD:SW_SPST_SKQG_WithoutStem","Alps Alpine","SKQGABE010","1",""
"SW2","BOOT","Button_Switch_SMD:SW_SPST_SKQG_WithoutStem","Alps Alpine","SKQGABE010","1",""
"SW3","USER","Button_Switch_SMD:SW_SPST_SKQG_WithoutStem","Alps Alpine","SKQGABE010","1",""
"SW4","SYSTEM POWER","Button_Switch_THT:SW_Slide_SPDT_Angled_CK_OS102011MA1Q","C&K","OS102011MA1QN1","1",""
"TP1","VBUS_PROTECTED","TestPoint:TestPoint_Pad_D1.0mm","","","1","yes"
"TP2","3V3","TestPoint:TestPoint_Pad_D1.0mm","","","1","yes"
"TP3","GND","TestPoint:TestPoint_Pad_D1.0mm","","","1","yes"
"TP4","UART0_TX","TestPoint:TestPoint_Pad_D1.0mm","","","1","yes"
"TP5","UART0_RX","TestPoint:TestPoint_Pad_D1.0mm","","","1","yes"
"TP6","BAT_CELL","TestPoint:TestPoint_Pad_D1.0mm","","","1","yes"
"TP7","SYS_5V","TestPoint:TestPoint_Pad_D1.0mm","","","1","yes"
"TP8","RX5808_RSSI_ADC","TestPoint:TestPoint_Pad_D1.0mm","","","1","yes"
"U1","ESP32-S3-WROOM-1-N16R8","RF_Module:ESP32-S3-WROOM-1","Espressif Systems","ESP32-S3-WROOM-1-N16R8","1",""
"U2","USBLC6-2SC6","Package_TO_SOT_SMD:SOT-23-6","STMicroelectronics","USBLC6-2SC6","1",""
"U3","AP63203WU-7","Package_TO_SOT_SMD:TSOT-23-6","Diodes Incorporated","AP63203WU-7","1",""
"U4","BQ24074RGTR","Package_DFN_QFN:VQFN-16-1EP_3x3mm_P0.5mm_EP1.6x1.6mm","Texas Instruments","BQ24074RGTR","1",""
"U5","TPS61232DRCR","Package_SON:Texas_S-PVSON-N10_ThermalVias","Texas Instruments","TPS61232DRCR","1",""
"U6","MAX17048G+T10","Package_DFN_QFN:DFN-8-1EP_2x2mm_P0.5mm_EP0.9x1.3mm","Analog Devices","MAX17048G+T10","1",""

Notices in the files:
README.md:
License: GPL v3
hardware/rev_b/skysweep32_pro_rev_b.kicad_pcb:
GPL-3.0-only | github.com/bobberdolle1/SkySweep32
hardware/skysweep32_pro.kicad_pcb:
GPL-3.0 License — Open Hardware
v1.1  2026-08-10  GPL-3.0
